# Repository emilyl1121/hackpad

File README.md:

# HackPad
YSWS for athena award and highway
My hackpad has 4 keys and each key is for play music, skip music, mute& unmute, and screenshot! These are the most used keys on my laptop.

## CAD

The overall CAD of my hacpad design ↑ (designed in Fusion)

## PCB

## Schematic

designed in KiCAD

## Firmware:

I used QMK firmware and the QMK configurator to edit the keys

## BOM:

I used these components in the project:
- 1x XIAO RP2040
- 1x Case (2 printed parts)
- 2x SK6812 MINI-E LEDs 
- 4x Blank DSA keycaps

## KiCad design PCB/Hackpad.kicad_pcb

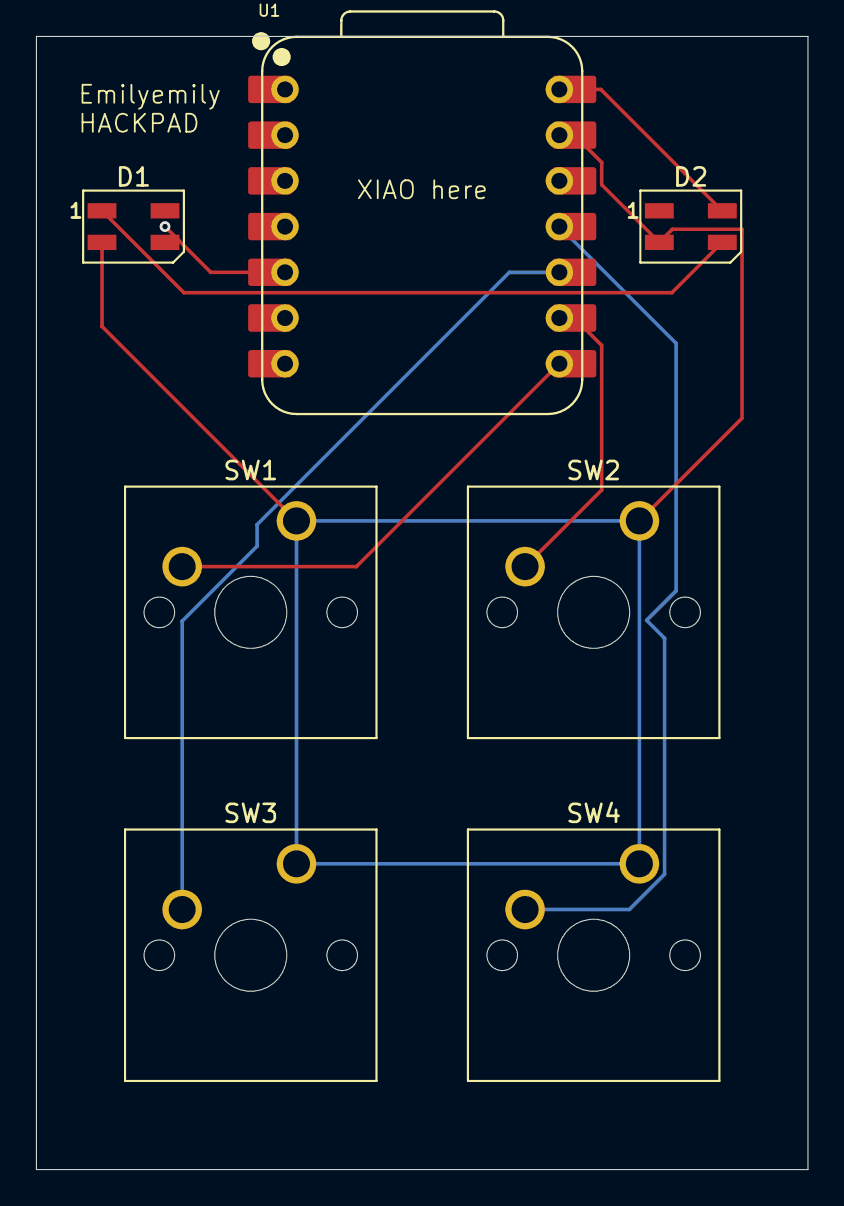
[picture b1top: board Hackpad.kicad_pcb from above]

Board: 2 copper layers, 42.9 x 63.0 mm, 7 parts (0 on the bottom side), 8 nets.

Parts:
D1, D2: SK6812; LED_SK6812MINI_PLCC4_3.5x3.5mm_P1.75mm
SW1, SW2, SW3, SW4: SW_Push; SW_Cherry_MX_1.00u_PCB
U1: XIAO-RP2040-DIP

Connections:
+5V: D2.4 (DOUT), U1.14 (VBUS)
GND: D1.2 (DIN), D2.2 (DIN), SW1.1, SW2.1, SW3.1, SW4.1, U1.13 (GND)
unnamed: D1.3 (VDD), U1.5 (GPIO6/SDA)
unnamed: D1.1 (VSS), D2.3 (VDD)
unnamed: SW1.2, U1.8 (GPIO1/RX)
unnamed: SW2.2, U1.9 (GPIO2/SCK)
unnamed: SW4.2, U1.11 (GPIO3/MOSI)
unnamed: SW3.2, U1.10 (GPIO4/MISO)

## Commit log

2025-05-24 Adding files
2025-06-09 Update README.md
    Added necessary descriptions and screenshots
2025-06-09 Add CAD STEP files
2025-06-09 Create folder
2025-06-09 Add PCB files via upload
2025-06-09 Create CAD folder
2025-06-09 Add CAD files via Upload
2025-06-09 Create firmware
